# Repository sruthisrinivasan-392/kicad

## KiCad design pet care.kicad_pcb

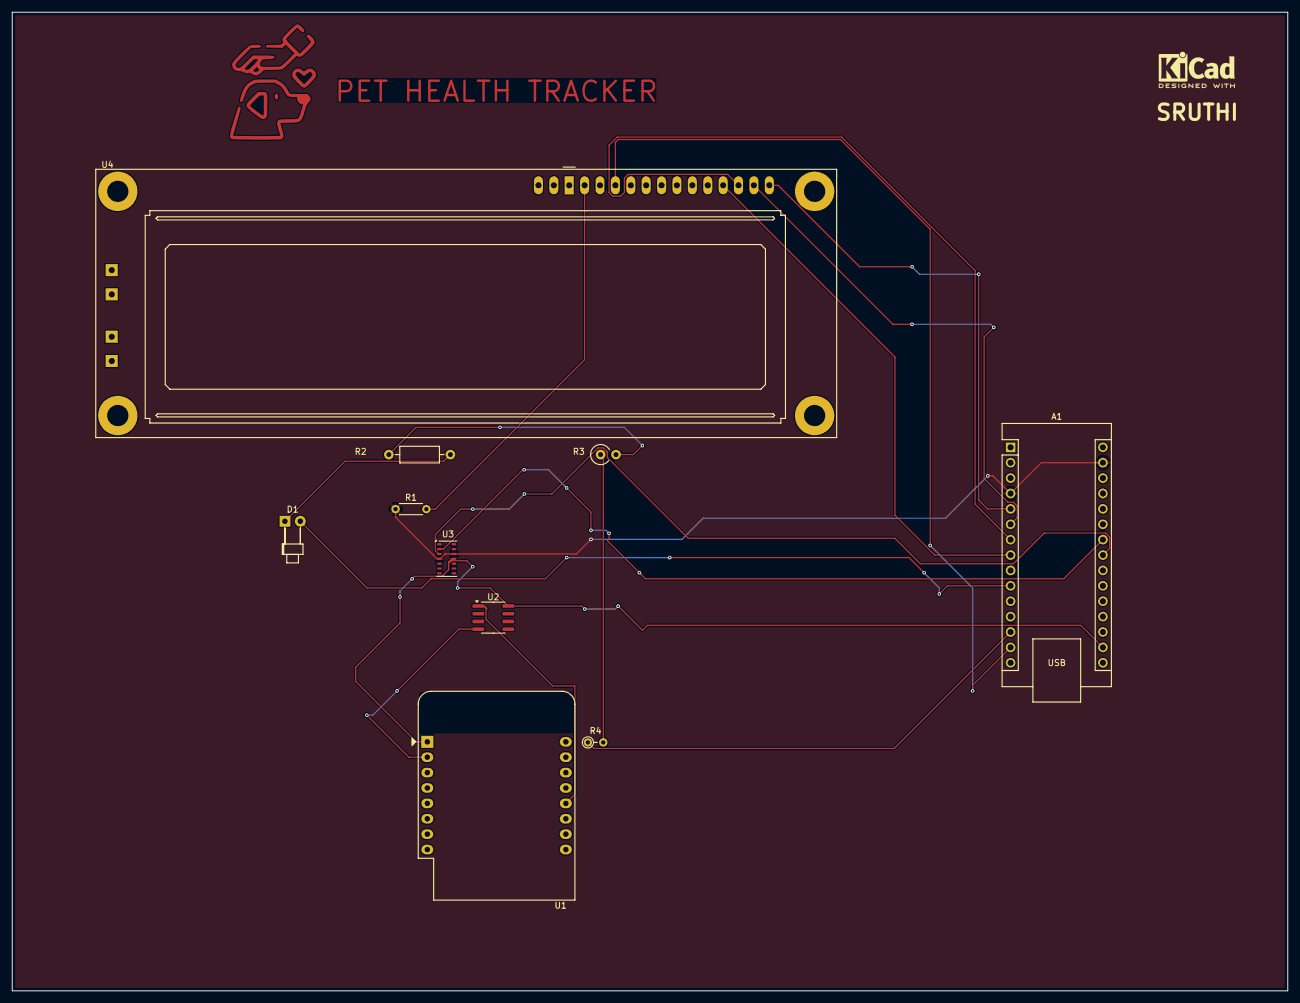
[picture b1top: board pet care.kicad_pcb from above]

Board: 2 copper layers, 210.5 x 161.5 mm, 10 parts (0 on the bottom side), 17 nets.

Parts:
A1: Arduino_Nano_Every; Arduino_Nano
D1: LED; LED_D1.8mm_W1.8mm_H2.4mm_Horizontal_O3.81mm_Z8.2mm
R1: R; R_Axial_DIN0204_L3.6mm_D1.6mm_P5.08mm_Horizontal
R2: R; R_Axial_DIN0207_L6.3mm_D2.5mm_P10.16mm_Horizontal
R3: R; R_Axial_DIN0309_L9.0mm_D3.2mm_P2.54mm_Vertical
R4: R; R_Axial_DIN0204_L3.6mm_D1.6mm_P2.54mm_Vertical
U1: Olimex_MOD-WIFI-ESP8266-DEV; WEMOS_D1_mini_light
U2: TMP36xS; SOIC-8_3.9x4.9mm_P1.27mm
U3: MAX30102; Maxim_OLGA-14_3.3x5.6mm_P0.8mm
U4: LCD-016N002L

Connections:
unnamed: A1.17 (3V3), U1.1 (3.3V), U2.8 (+Vs), U3.11 (VDD)
unnamed: A1.5 (D2), U4.14 (DB7)
unnamed: A1.6 (D3), U4.13 (DB6)
unnamed: A1.7 (D4), U4.12 (DB5)
unnamed: A1.8 (D5), U4.11 (DB4)
unnamed: A1.10 (D7), D1.2 (A)
unnamed: A1.13 (D10), R4.1
unnamed: A1.14 (MOSI), U4.4 (RS)
unnamed: A1.24 (SCL/A5), U3.2 (SCL)
unnamed: A1.23 (SDA/A4), U3.3 (SDA)
unnamed: D1.1 (K), R2.2
unnamed: R2.1, R3.2
unnamed: R3.1, R4.2
unnamed: U1.12 (ADC), U2.1 (V_{OUT})
unnamed: U1.2 (GND), U2.4 (GND)
unnamed: A1.4 (GND), A1.29 (GND), R1.1, U3.4 (PGND), U3.12 (GND)
unnamed: R1.2, U4.2 (VDD)
